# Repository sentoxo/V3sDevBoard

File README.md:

# V3sDevBoard
Educational project of first PCB desgin, SBC with linux built on allwinner V3s SoC.  

## SYSTEM SPECIFICATIONS
=====================

### CORE SYSTEM:
- CPU: Allwinner V3s (ARM Cortex-A7 @ 1.2GHz)
- RAM: 64MB DDR2 @ 400MHz (Integrated SiP)
- STORAGE: SD Interface for OS (SDIO compatible)

### CONNECTIVITY:
- ETHERNET: 100Mbps Interface
- WIRELESS: WiFi & Bluetooth (via ESP32[ESP-Hosted-NG] on SDIO/UART) {PG0-5 -> SDIO, PB0-1 -> UART}
- LONG RANGE: LoRa support (via Ra-02 on SPI) {PB2 -> RESET, PB3 -> INT, PC0-3 -> SPI}
- USB: USB Host support (Simple)
- DEBUG: System UARTs to USB bridge

### DISPLAY & IMAGING:
- CAMERA: MIPI CSI (22-pin connector)
- LCD: RGB-666 Interface with backlight support (40-pin) [ST7280] {PB4 -> LC_LED_PWM, PE0-19,23-24}

### SENSORS & I/O:
- MOTION: MPU6050 Accelerometer & Gyroscope [I2C] {PB6-7}
- ENVIRONMENT: BME280 Sensor (Temp/Press/Hum) [I2C] {PB6-7}
- AUDIO: 3.5mm Audio Jack
- INPUT: Low-resolution ADC for button matrix (6 buttons)
- VISUAL: PCB RGB backlight WS2812B {PB5}

### POWER & SOFTWARE:
- REGULATION: DC-DC converters for 3.3V, 1.8V, 1.2V
- OPERATING SYSTEM: Powered by custom Mainline Linux

=====================
## Errata for revA
- Ther was mistake in SDIO for SDCard. Swaped data lines.
- RTC didn't have power without battery.

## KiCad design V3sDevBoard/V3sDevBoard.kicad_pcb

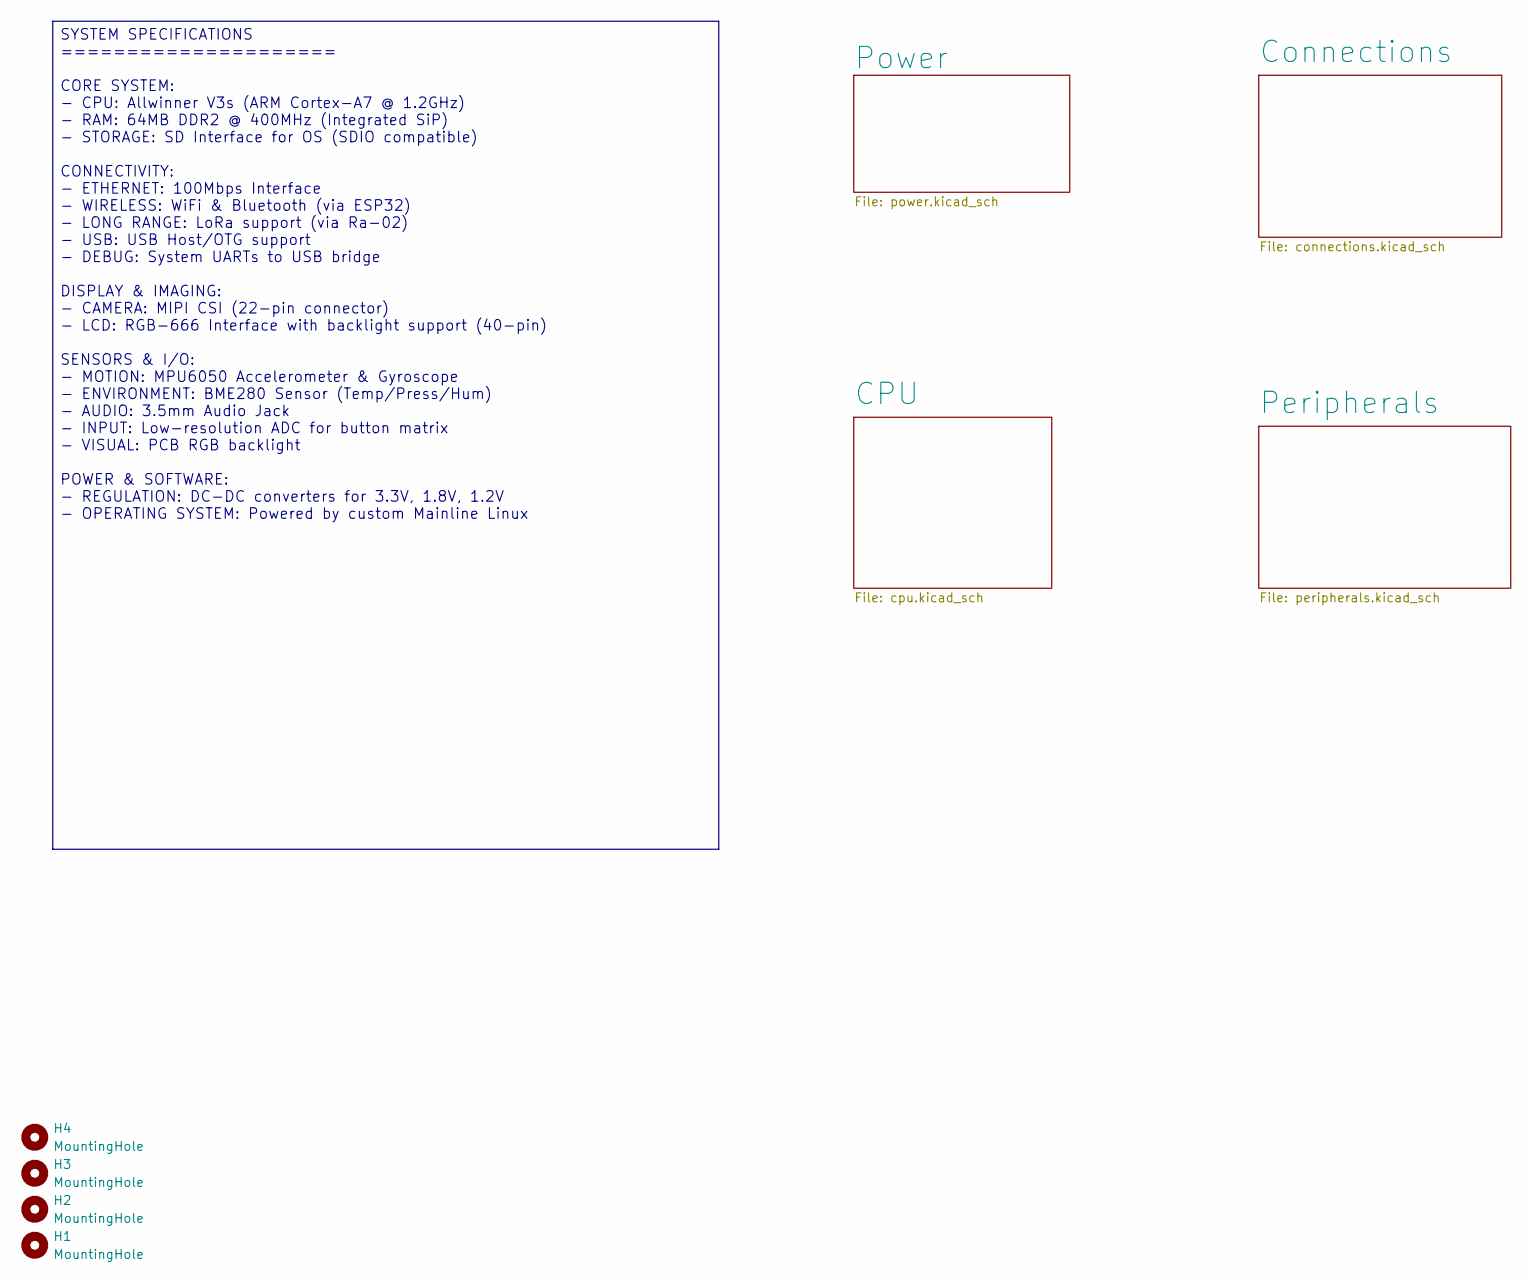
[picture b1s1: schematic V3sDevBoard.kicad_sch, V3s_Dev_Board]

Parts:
H1, H2, H3, H4: MountingHole; MountingHole_3.2mm_M3

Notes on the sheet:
SYSTEM SPECIFICATIONS ===================== CORE SYSTEM: - CPU: Allwinner V3s (ARM Cortex-A7 @ 1.2GHz) - RAM: 64MB DDR2 @ 400MHz (Integrated SiP) - STORAGE: SD Interface for OS (SDIO compatible) CONNECTIVITY: - ETHERNET: 100Mbps Interface - WIRELESS: WiFi & Bluetooth (via ESP32) - LONG RANGE: LoRa 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

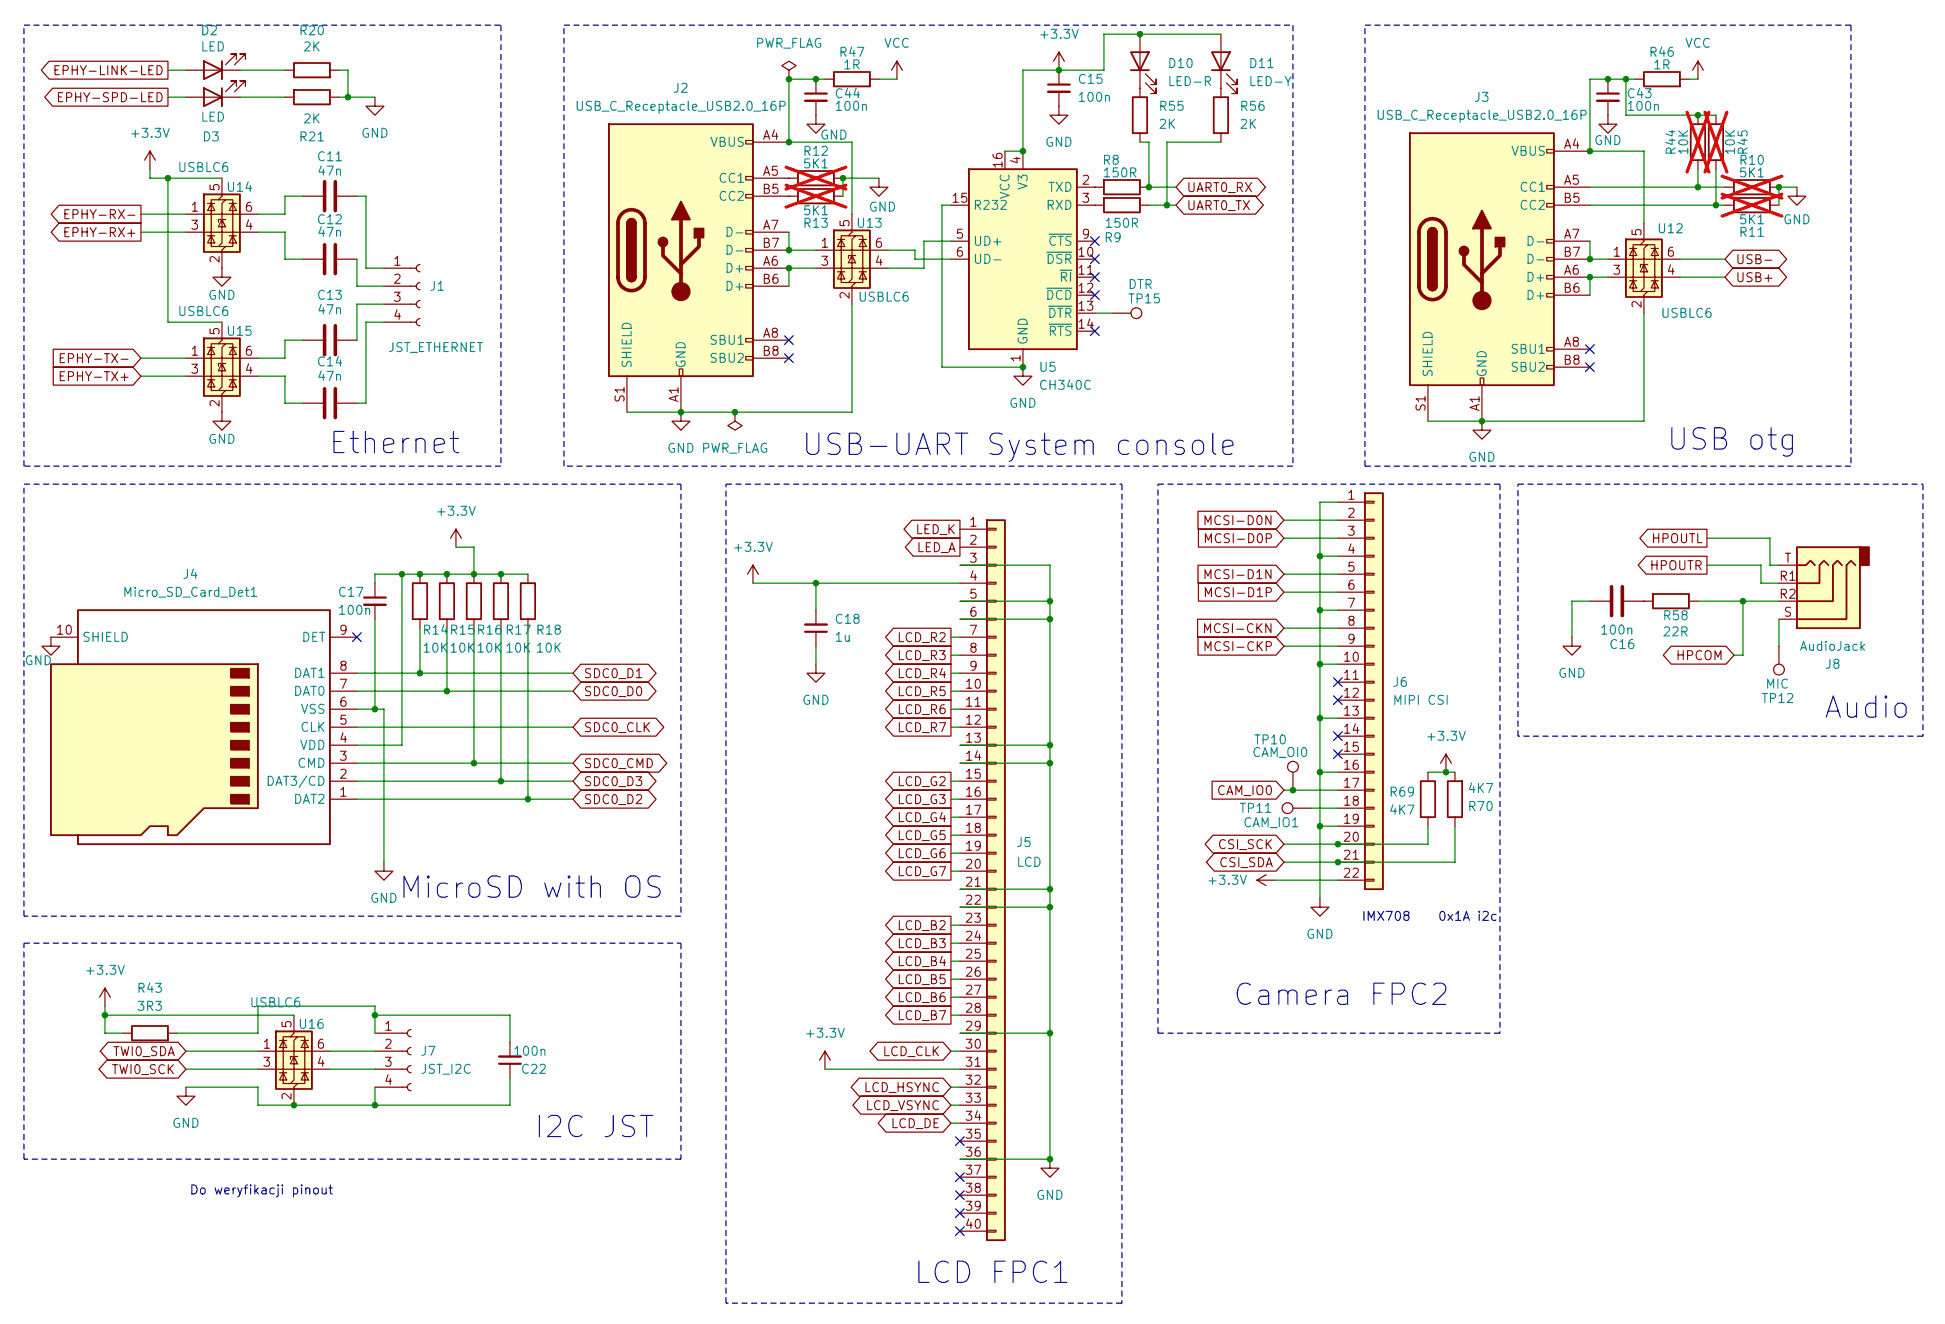
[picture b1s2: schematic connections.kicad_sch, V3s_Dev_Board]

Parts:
C11, C12, C13, C14: 47n; C_0805_2012Metric_Pad1.18x1.45mm_HandSolder
C15, C16, C17, C22: 100n; C_0805_2012Metric_Pad1.18x1.45mm_HandSolder
C18: 1u; C_0805_2012Metric_Pad1.18x1.45mm_HandSolder
C43, C44: 100n; C_0603_1608Metric_Pad1.08x0.95mm_HandSolder
D2, D3: LED; LED_0805_2012Metric_Pad1.15x1.40mm_HandSolder
D10: LED-R; LED_0805_2012Metric_Pad1.15x1.40mm_HandSolder
D11: LED-Y; LED_0805_2012Metric_Pad1.15x1.40mm_HandSolder
J1: JST_ETHERNET; JST_GH_BM04B-GHS-TBT_1x04-1MP_P1.25mm_Vertical
J2, J3: USB_C_Receptacle_USB2.0_16P; USB_C_Receptacle_GCT_USB4105-xx-A_16P_TopMnt_Horizontal
J4: Micro_SD_Card_Det1; microSD
J5: LCD; Amphenol_F32Q-1A7x1-11040_1x40-1MP_P0.5mm_Horizontal
J6: MIPI CSI; FPC_1x22-1MP_P0.5mm_Vertical
J7: JST_I2C; JST_GH_BM04B-GHS-TBT_1x04-1MP_P1.25mm_Vertical
J8: AudioJack; Jack_3.5mm_PJ320D_Horizontal
R8, R9: 150R; R_0603_1608Metric_Pad0.98x0.95mm_HandSolder
R10, R11, R12, R13: 5K1; R_0603_1608Metric_Pad0.98x0.95mm_HandSolder; not fitted
R14, R15, R16, R17, R18: 10K; R_0603_1608Metric_Pad0.98x0.95mm_HandSolder
R20, R21, R55, R56: 2K; R_0603_1608Metric_Pad0.98x0.95mm_HandSolder
R43: 3R3; R_0805_2012Metric_Pad1.20x1.40mm_HandSolder
R44, R45: 10K; R_0603_1608Metric_Pad0.98x0.95mm_HandSolder; not fitted
R46, R47: 1R; R_0805_2012Metric
R58: 22R; R_0603_1608Metric_Pad0.98x0.95mm_HandSolder
R69, R70: 4K7; R_0603_1608Metric_Pad0.98x0.95mm_HandSolder
TP10: CAM_OI0; TestPoint_Pad_D1.0mm
TP11: CAM_IO1; TestPoint_Pad_D1.0mm
TP12: MIC; TestPoint_Pad_D1.0mm
TP15: DTR; TestPoint_Pad_D1.0mm
U5: CH340C; SOIC-16_3.9x9.9mm_P1.27mm
U12, U13, U14, U15, U16: USBLC6; SOT-23-6

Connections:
+3.3V: C15.1, C17.1, C18.2, D10.2 (A), D11.2 (A), J4.4 (VDD), J5.4, J5.31, J6.22, R14.1, R15.1, R16.1, R17.1, R18.1, R43.1, R69.1, R70.2, U5.4 (V3), U5.16 (VCC), U14.5 (VBUS), U15.5 (VBUS), U16.5 (VBUS); also elsewhere on the board
CAM_IO0: J6.17, TP10.1 (1_1); also elsewhere on the board
CSI_SCK: J6.20, R69.2; also elsewhere on the board
CSI_SDA: J6.21, R70.1; also elsewhere on the board
EPHY-LINK-LED: D2.2 (A); also elsewhere on the board
EPHY-RX+: U14.3 (I/O2); also elsewhere on the board
EPHY-RX-: U14.1 (I/O1); also elsewhere on the board
EPHY-SPD-LED: D3.2 (A); also elsewhere on the board
EPHY-TX+: U15.3 (I/O2); also elsewhere on the board
EPHY-TX-: U15.1 (I/O1); also elsewhere on the board
GND: C15.2, C16.2, C17.2, C18.1, C22.1, C43.2, C44.2, J2.A1 (GND), J2.A12 (GND), J2.B1 (GND), J2.B12 (GND), J2.S1 (SHIELD), J3.A1 (GND), J3.A12 (GND), J3.B1 (GND), J3.B12 (GND), J3.S1 (SHIELD), J4.6 (VSS), J4.10 (SHIELD), J5.3, J5.5, J5.6, J5.13, J5.14, J5.21, J5.22, J5.29, J5.36, J6.1, J6.4, J6.7, J6.10, J6.13, J6.16, J6.19, J7.4, R10.2, R11.1, R12.2, R13.1, R20.2, R21.1, U5.1 (GND), U5.15 (R232), U12.2 (GND), U13.2 (GND), U14.2 (GND), U15.2 (GND), U16.2 (GND); also elsewhere on the board
HPCOM: J8.R2, R58.1; also elsewhere on the board
HPOUTL: J8.T; also elsewhere on the board
HPOUTR: J8.R1; also elsewhere on the board
LCD_B2: J5.23; also elsewhere on the board
LCD_B3: J5.24; also elsewhere on the board
LCD_B4: J5.25; also elsewhere on the board
LCD_B5: J5.26; also elsewhere on the board
LCD_B6: J5.27; also elsewhere on the board
LCD_B7: J5.28; also elsewhere on the board
LCD_CLK: J5.30; also elsewhere on the board
LCD_DE: J5.34; also elsewhere on the board
LCD_G2: J5.15; also elsewhere on the board
LCD_G3: J5.16; also elsewhere on the board
LCD_G4: J5.17; also elsewhere on the board
LCD_G5: J5.18; also elsewhere on the board
LCD_G6: J5.19; also elsewhere on the board
LCD_G7: J5.20; also elsewhere on the board
LCD_HSYNC: J5.32; also elsewhere on the board
LCD_R2: J5.7; also elsewhere on the board
LCD_R3: J5.8; also elsewhere on the board
LCD_R4: J5.9; also elsewhere on the board
LCD_R5: J5.10; also elsewhere on the board
LCD_R6: J5.11; also elsewhere on the board
LCD_R7: J5.12; also elsewhere on the board
LCD_VSYNC: J5.33; also elsewhere on the board
LED_A: J5.2; also elsewhere on the board
LED_K: J5.1; also elsewhere on the board
MCSI-CKN: J6.8; also elsewhere on the board
MCSI-CKP: J6.9; also elsewhere on the board
MCSI-D0N: J6.2; also elsewhere on the board
MCSI-D0P: J6.3; also elsewhere on the board
MCSI-D1N: J6.5; also elsewhere on the board
MCSI-D1P: J6.6; also elsewhere on the board
unnamed: C11.1, U14.6 (I/O1)
unnamed: C12.1, U14.4 (I/O2)
unnamed: C13.1, U15.6 (I/O1)
unnamed: C14.1, U15.4 (I/O2)
unnamed: C16.1, R58.2
unnamed: D2.1 (K), R20.1
unnamed: D3.1 (K), R21.2
unnamed: D10.1 (K), R55.1
unnamed: D11.1 (K), R56.1
unnamed: C11.2, J1.1
unnamed: C12.2, J1.2
unnamed: C13.2, J1.3
unnamed: C14.2, J1.4
unnamed: J2.A5 (CC1), R12.1
unnamed: J2.B5 (CC2), R13.2
unnamed: J2.A6 (D+), J2.B6 (D+), U13.3 (I/O2)
unnamed: J2.A7 (D-), J2.B7 (D-), U13.1 (I/O1)
unnamed: J3.A5 (CC1), R10.1, R44.1
unnamed: J3.B5 (CC2), R11.2, R45.2
unnamed: J3.A6 (D+), J3.B6 (D+), U12.3 (I/O2)
unnamed: J3.A7 (D-), J3.B7 (D-), U12.1 (I/O1)
unnamed: J6.18, TP11.1 (1_1)
unnamed: C22.2, J7.1, R43.2
unnamed: J7.2, U16.6 (I/O1)
unnamed: J7.3, U16.4 (I/O2)
unnamed: J8.S, TP12.1 (1_1)
unnamed: R9.2, U5.3 (RXD)
unnamed: R8.2, U5.2 (TXD)
unnamed: U5.5 (UD+), U13.4 (I/O2)
unnamed: U5.6 (UD-), U13.6 (I/O1)
unnamed: TP15.1 (1_1), U5.13 (~DTR)
unnamed: C43.1, J3.A4 (VBUS), J3.A9 (VBUS), J3.B4 (VBUS), J3.B9 (VBUS), R44.2, R45.1, R46.1, U12.5 (VBUS)
unnamed: C44.1, J2.A4 (VBUS), J2.A9 (VBUS), J2.B4 (VBUS), J2.B9 (VBUS), R47.1, U13.5 (VBUS)
SDC0_CLK: J4.5 (CLK); also elsewhere on the board
SDC0_CMD: J4.3 (CMD), R16.2; also elsewhere on the board
SDC0_D0: J4.7 (DAT0), R15.2; also elsewhere on the board
SDC0_D1: J4.8 (DAT1), R14.2; also elsewhere on the board
SDC0_D2: J4.1 (DAT2), R18.2; also elsewhere on the board
SDC0_D3: J4.2 (DAT3/CD), R17.2; also elsewhere on the board
TWI0_SCK: U16.3 (I/O2); also elsewhere on the board
TWI0_SDA: U16.1 (I/O1); also elsewhere on the board
UART0_RX: R8.1, R55.2; also elsewhere on the board
UART0_TX: R9.1, R56.2; also elsewhere on the board
USB+: U12.4 (I/O2); also elsewhere on the board
USB-: U12.6 (I/O1); also elsewhere on the board
VCC: R46.2, R47.2; also elsewhere on the board

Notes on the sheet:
MicroSD with OS
LCD FPC1
Ethernet
Camera FPC2
USB otg
Audio
IMX708 0x1A i2c
USB-UART System console
Do weryfikacji pinout
I2C JST

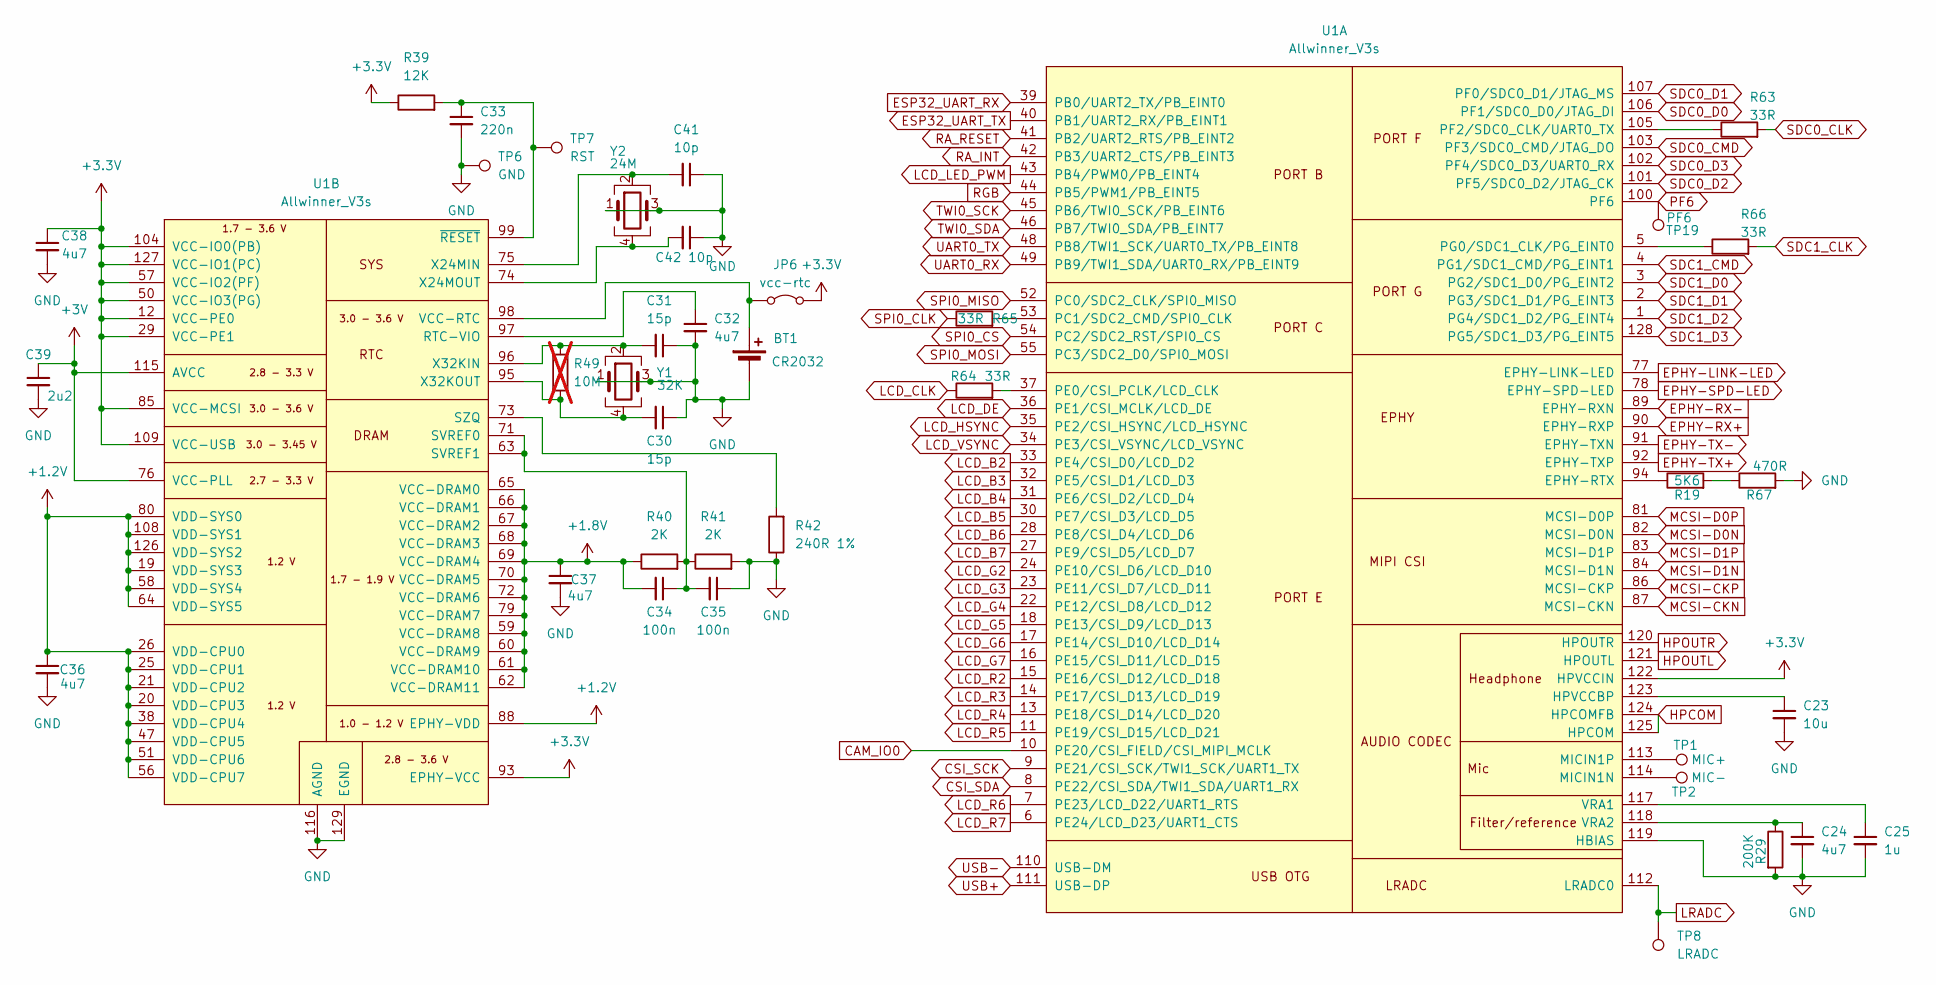
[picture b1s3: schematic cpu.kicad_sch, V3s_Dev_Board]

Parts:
BT1: CR2032; PinHeader_1x02_P1.00mm_Vertical_SMD_Pin1Right
C23: 10u; C_0805_2012Metric_Pad1.18x1.45mm_HandSolder
C24, C32, C36, C37, C38: 4u7; C_0805_2012Metric_Pad1.18x1.45mm_HandSolder
C25: 1u; C_0805_2012Metric_Pad1.18x1.45mm_HandSolder
C30, C31: 15p; C_0603_1608Metric_Pad1.08x0.95mm_HandSolder
C33: 220n; C_0603_1608Metric_Pad1.08x0.95mm_HandSolder
C34, C35: 100n; C_0603_1608Metric_Pad1.08x0.95mm_HandSolder
C39: 2u2; C_0805_2012Metric_Pad1.18x1.45mm_HandSolder
C41, C42: 10p; C_0603_1608Metric_Pad1.08x0.95mm_HandSolder
JP6: vcc-rtc; SolderJumper-2_P1.3mm_Bridged_RoundedPad1.0x1.5mm
R19: 5K6; R_0603_1608Metric_Pad0.98x0.95mm_HandSolder
R29: 200K; R_0603_1608Metric_Pad0.98x0.95mm_HandSolder
R39: 12K; R_0603_1608Metric_Pad0.98x0.95mm_HandSolder
R40, R41: 2K; R_0603_1608Metric_Pad0.98x0.95mm_HandSolder
R42: 240R 1%; R_0603_1608Metric_Pad0.98x0.95mm_HandSolder
R49: 10M; R_0603_1608Metric_Pad0.98x0.95mm_HandSolder; not fitted
R63, R64, R65, R66: 33R; R_0603_1608Metric_Pad0.98x0.95mm_HandSolder
R67: 470R; R_0603_1608Metric_Pad0.98x0.95mm_HandSolder
TP1: MIC+; TestPoint_Pad_1.0x1.0mm
TP2: MIC-; TestPoint_Pad_1.0x1.0mm
TP6: GND; TestPoint_Pad_D1.5mm
TP7: RST; TestPoint_Pad_D1.5mm
TP8: LRADC; TestPoint_Pad_D1.0mm
TP19: PF6; TestPoint_Pad_D1.0mm
U1: Allwinner_V3s; eLQFP-128_14x14_Pitch0.4mm_EPAD_6.60mm
Y1: 32K; Crystal_SMD_3225-4Pin_3.2x2.5mm_HandSoldering
Y2: 24M; Crystal_SMD_3225-4Pin_3.2x2.5mm_HandSoldering

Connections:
+1.2V: C36.1, U1.19 (VDD-SYS3), U1.20 (VDD-CPU3), U1.21 (VDD-CPU2), U1.25 (VDD-CPU1), U1.26 (VDD-CPU0), U1.38 (VDD-CPU4), U1.47 (VDD-CPU5), U1.51 (VDD-CPU6), U1.56 (VDD-CPU7), U1.58 (VDD-SYS4), U1.64 (VDD-SYS5), U1.80 (VDD-SYS0), U1.88 (EPHY-VDD), U1.108 (VDD-SYS1), U1.126 (VDD-SYS2); also elsewhere on the board
+1.8V: C34.2, C37.1, R40.1, U1.59 (VCC-DRAM8), U1.60 (VCC-DRAM9), U1.61 (VCC-DRAM10), U1.62 (VCC-DRAM11), U1.65 (VCC-DRAM0), U1.66 (VCC-DRAM1), U1.67 (VCC-DRAM2), U1.68 (VCC-DRAM3), U1.69 (VCC-DRAM4), U1.70 (VCC-DRAM5), U1.72 (VCC-DRAM6), U1.79 (VCC-DRAM7); also elsewhere on the board
+3.3V: C38.1, JP6.2 (B), R39.1, U1.12 (VCC-PE0), U1.29 (VCC-PE1), U1.50 (VCC-IO3(PG)), U1.57 (VCC-IO2(PF)), U1.85 (VCC-MCSI), U1.93 (EPHY-VCC), U1.104 (VCC-IO0(PB)), U1.109 (VCC-USB), U1.122 (HPVCCIN), U1.127 (VCC-IO1(PC)); also elsewhere on the board
+3V: C39.1, U1.76 (VCC-PLL), U1.115 (AVCC); also elsewhere on the board
CAM_IO0: U1.10 (PE20/CSI_FIELD/CSI_MIPI_MCLK); also elsewhere on the board
CSI_SCK: U1.9 (PE21/CSI_SCK/TWI1_SCK/UART1_TX); also elsewhere on the board
CSI_SDA: U1.8 (PE22/CSI_SDA/TWI1_SDA/UART1_RX); also elsewhere on the board
EPHY-LINK-LED: U1.77 (EPHY-LINK-LED); also elsewhere on the board
EPHY-RX+: U1.90 (EPHY-RXP); also elsewhere on the board
EPHY-RX-: U1.89 (EPHY-RXN); also elsewhere on the board
EPHY-SPD-LED: U1.78 (EPHY-SPD-LED); also elsewhere on the board
EPHY-TX+: U1.92 (EPHY-TXP); also elsewhere on the board
EPHY-TX-: U1.91 (EPHY-TXN); also elsewhere on the board
ESP32_UART_RX: U1.39 (PB0/UART2_TX/PB_EINT0); also elsewhere on the board
ESP32_UART_TX: U1.40 (PB1/UART2_RX/PB_EINT1); also elsewhere on the board
GND: BT1.2 (-), C23.2, C24.2, C25.2, C30.1, C31.1, C32.2, C33.2, C35.1, C36.2, C37.2, C38.2, C39.2, C41.1, C42.1, R29.2, R41.2, R42.1, R67.2, TP6.1 (1_1), U1.116 (AGND), U1.119 (HBIAS), U1.129 (EGND), Y1.1, Y1.3, Y2.1, Y2.3; also elsewhere on the board
HPCOM: U1.124 (HPCOMFB), U1.125 (HPCOM); also elsewhere on the board
HPOUTL: U1.121 (HPOUTL); also elsewhere on the board
HPOUTR: U1.120 (HPOUTR); also elsewhere on the board
LCD_B2: U1.33 (PE4/CSI_D0/LCD_D2); also elsewhere on the board
LCD_B3: U1.32 (PE5/CSI_D1/LCD_D3); also elsewhere on the board
LCD_B4: U1.31 (PE6/CSI_D2/LCD_D4); also elsewhere on the board
LCD_B5: U1.30 (PE7/CSI_D3/LCD_D5); also elsewhere on the board
LCD_B6: U1.28 (PE8/CSI_D4/LCD_D6); also elsewhere on the board
LCD_B7: U1.27 (PE9/CSI_D5/LCD_D7); also elsewhere on the board
LCD_CLK: R64.1; also elsewhere on the board
LCD_DE: U1.36 (PE1/CSI_MCLK/LCD_DE); also elsewhere on the board
LCD_G2: U1.24 (PE10/CSI_D6/LCD_D10); also elsewhere on the board
LCD_G3: U1.23 (PE11/CSI_D7/LCD_D11); also elsewhere on the board
LCD_G4: U1.22 (PE12/CSI_D8/LCD_D12); also elsewhere on the board
LCD_G5: U1.18 (PE13/CSI_D9/LCD_D13); also elsewhere on the board
LCD_G6: U1.17 (PE14/CSI_D10/LCD_D14); also elsewhere on the board
LCD_G7: U1.16 (PE15/CSI_D11/LCD_D15); also elsewhere on the board
LCD_HSYNC: U1.35 (PE2/CSI_HSYNC/LCD_HSYNC); also elsewhere on the board
LCD_LED_PWM: U1.43 (PB4/PWM0/PB_EINT4); also elsewhere on the board
LCD_R2: U1.15 (PE16/CSI_D12/LCD_D18); also elsewhere on the board
LCD_R3: U1.14 (PE17/CSI_D13/LCD_D19); also elsewhere on the board
LCD_R4: U1.13 (PE18/CSI_D14/LCD_D20); also elsewhere on the board
LCD_R5: U1.11 (PE19/CSI_D15/LCD_D21); also elsewhere on the board
LCD_R6: U1.7 (PE23/LCD_D22/UART1_RTS); also elsewhere on the board
LCD_R7: U1.6 (PE24/LCD_D23/UART1_CTS); also elsewhere on the board
LCD_VSYNC: U1.34 (PE3/CSI_VSYNC/LCD_VSYNC); also elsewhere on the board
LRADC: TP8.1 (1_1), U1.112 (LRADC0); also elsewhere on the board
MCSI-CKN: U1.87 (MCSI-CKN); also elsewhere on the board
MCSI-CKP: U1.86 (MCSI-CKP); also elsewhere on the board
MCSI-D0N: U1.82 (MCSI-D0N); also elsewhere on the board
MCSI-D0P: U1.81 (MCSI-D0P); also elsewhere on the board
MCSI-D1N: U1.84 (MCSI-D1N); also elsewhere on the board
MCSI-D1P: U1.83 (MCSI-D1P); also elsewhere on the board
unnamed: BT1.1 (+), JP6.1 (A), U1.98 (VCC-RTC)
unnamed: R19.2, R67.1
unnamed: R19.1, U1.94 (EPHY-RTX)
unnamed: C23.1, U1.123 (HPVCCBP)
unnamed: TP2.1 (1_1), U1.114 (MICIN1N)
unnamed: TP1.1 (1_1), U1.113 (MICIN1P)
unnamed: R65.2, U1.53 (PC1/SDC2_CMD/SPI0_CLK)
unnamed: R64.2, U1.37 (PE0/CSI_PCLK/LCD_CLK)
unnamed: R63.1, U1.105 (PF2/SDC0_CLK/UART0_TX)
unnamed: R66.1, U1.5 (PG0/SDC1_CLK/PG_EINT0)
unnamed: C25.1, U1.117 (VRA1)
unnamed: C24.1, R29.1, U1.118 (VRA2)
unnamed: C32.1, U1.97 (RTC-VIO)
unnamed: C34.1, C35.2, R40.2, R41.1, U1.63 (SVREF1), U1.71 (SVREF0)
unnamed: R42.2, U1.73 (SZQ)
unnamed: C41.2, U1.75 (X24MIN), Y2.2
unnamed: C42.2, U1.74 (X24MOUT), Y2.4
unnamed: C31.2, R49.2, U1.96 (X32KIN), Y1.2
unnamed: C30.2, R49.1, U1.95 (X32KOUT), Y1.4
unnamed: C33.1, R39.2, TP7.1 (1_1), U1.99 (~RESET)
PF6: TP19.1 (1_1), U1.100 (PF6); also elsewhere on the board
RA_INT: U1.42 (PB3/UART2_CTS/PB_EINT3); also elsewhere on the board
RA_RESET: U1.41 (PB2/UART2_RTS/PB_EINT2); also elsewhere on the board
RGB: U1.44 (PB5/PWM1/PB_EINT5); also elsewhere on the board
SDC0_CLK: R63.2; also elsewhere on the board
SDC0_CMD: U1.103 (PF3/SDC0_CMD/JTAG_DO); also elsewhere on the board
SDC0_D0: U1.106 (PF1/SDC0_D0/JTAG_DI); also elsewhere on the board
SDC0_D1: U1.107 (PF0/SDC0_D1/JTAG_MS); also elsewhere on the board
SDC0_D2: U1.101 (PF5/SDC0_D2/JTAG_CK); also elsewhere on the board
SDC0_D3: U1.102 (PF4/SDC0_D3/UART0_RX); also elsewhere on the board
SDC1_CLK: R66.2; also elsewhere on the board
SDC1_CMD: U1.4 (PG1/SDC1_CMD/PG_EINT1); also elsewhere on the board
SDC1_D0: U1.3 (PG2/SDC1_D0/PG_EINT2); also elsewhere on the board
SDC1_D1: U1.2 (PG3/SDC1_D1/PG_EINT3); also elsewhere on the board
SDC1_D2: U1.1 (PG4/SDC1_D2/PG_EINT4); also elsewhere on the board
SDC1_D3: U1.128 (PG5/SDC1_D3/PG_EINT5); also elsewhere on the board
SPI0_CLK: R65.1; also elsewhere on the board
SPI0_CS: U1.54 (PC2/SDC2_RST/SPI0_CS); also elsewhere on the board
SPI0_MISO: U1.52 (PC0/SDC2_CLK/SPI0_MISO); also elsewhere on the board
SPI0_MOSI: U1.55 (PC3/SDC2_D0/SPI0_MOSI); also elsewhere on the board
TWI0_SCK: U1.45 (PB6/TWI0_SCK/PB_EINT6); also elsewhere on the board
TWI0_SDA: U1.46 (PB7/TWI0_SDA/PB_EINT7); also elsewhere on the board
UART0_RX: U1.49 (PB9/TWI1_SDA/UART0_RX/PB_EINT9); also elsewhere on the board
UART0_TX: U1.48 (PB8/TWI1_SCK/UART0_TX/PB_EINT8); also elsewhere on the board
USB+: U1.111 (USB-DP); also elsewhere on the board
USB-: U1.110 (USB-DM); also elsewhere on the board

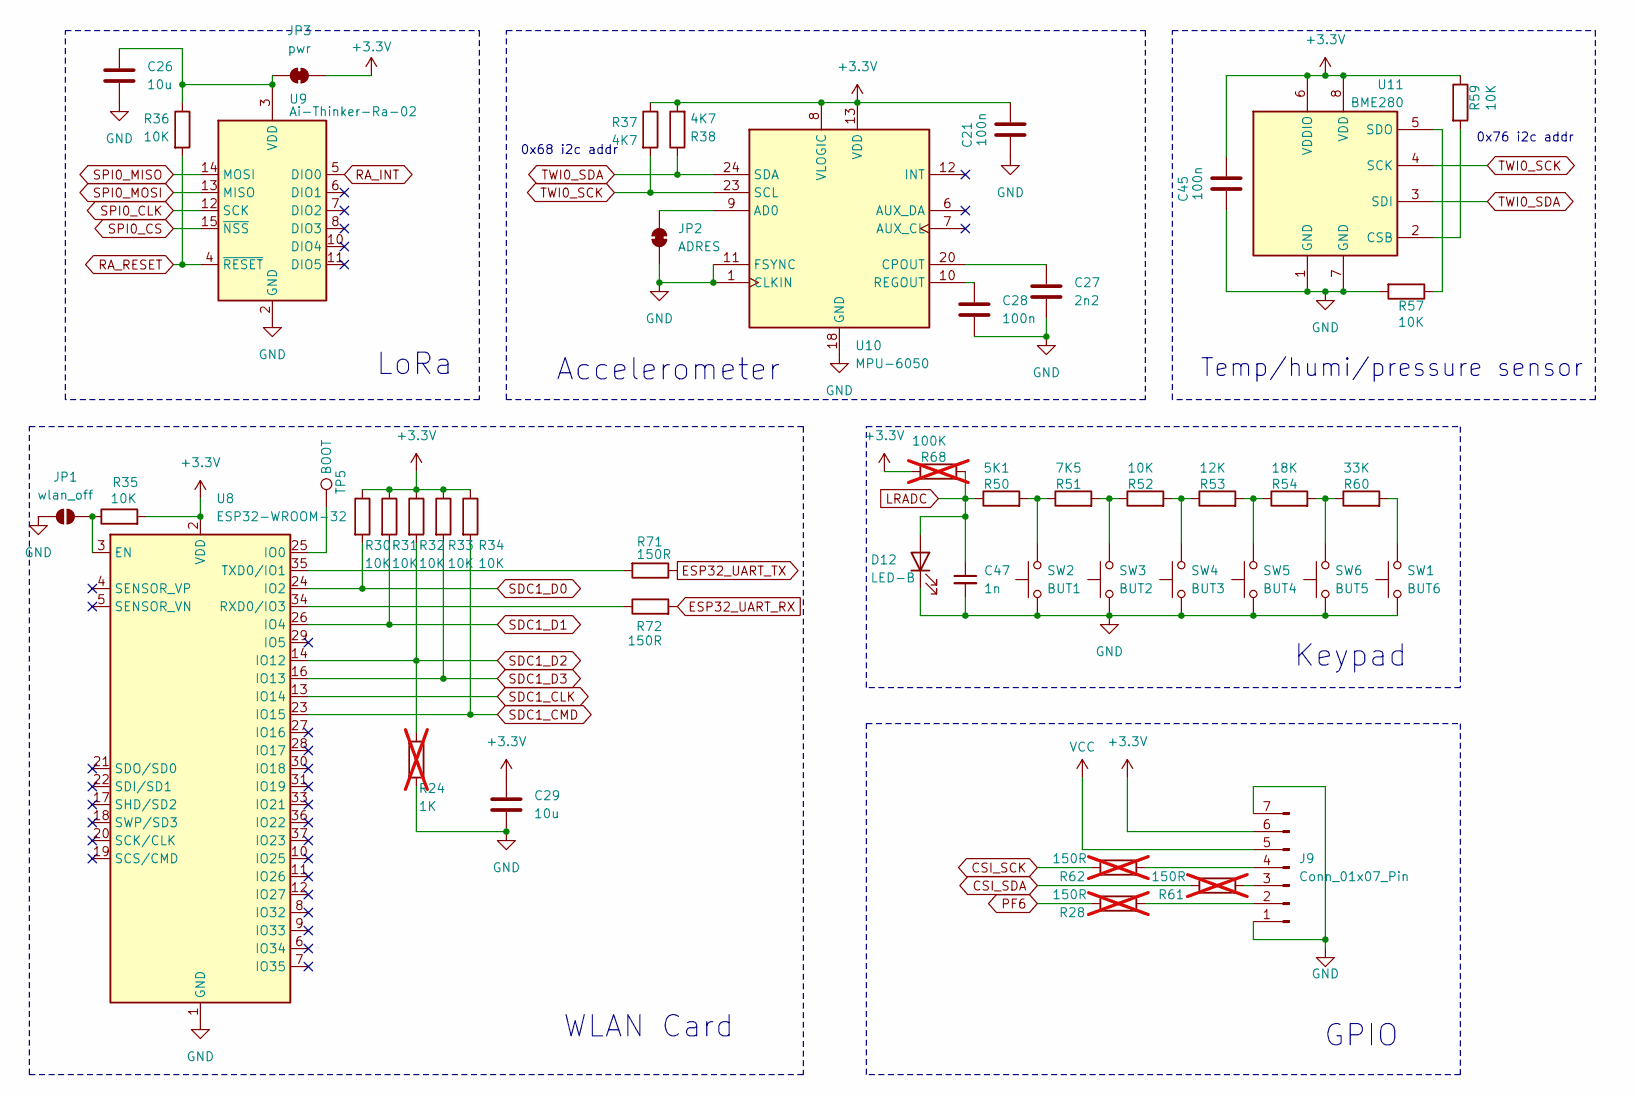
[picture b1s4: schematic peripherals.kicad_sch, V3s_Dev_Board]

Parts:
C21, C45: 100n; C_0805_2012Metric_Pad1.18x1.45mm_HandSolder
C26, C29: 10u; C_1206_3216Metric
C27: 2n2; C_0603_1608Metric_Pad1.08x0.95mm_HandSolder
C28: 100n; C_0603_1608Metric_Pad1.08x0.95mm_HandSolder
C47: 1n; C_0805_2012Metric_Pad1.18x1.45mm_HandSolder
D12: LED-B; LED_0805_2012Metric_Pad1.15x1.40mm_HandSolder
J9: Conn_01x07_Pin; PinHeader_1x07_P2.54mm_Vertical
JP1: wlan_off; SolderJumper-2_P1.3mm_Open_RoundedPad1.0x1.5mm
JP2: ADRES; SolderJumper-2_P1.3mm_Bridged_RoundedPad1.0x1.5mm
JP3: pwr; SolderJumper-2_P1.3mm_Bridged_RoundedPad1.0x1.5mm
R24: 1K; R_0603_1608Metric_Pad0.98x0.95mm_HandSolder; not fitted
R28, R61, R62: 150R; R_0603_1608Metric_Pad0.98x0.95mm_HandSolder; not fitted
R30, R31, R32, R33, R34, R35, R36, R52, R57, R59: 10K; R_0603_1608Metric_Pad0.98x0.95mm_HandSolder
R37, R38: 4K7; R_0603_1608Metric_Pad0.98x0.95mm_HandSolder
R50: 5K1; R_0603_1608Metric_Pad0.98x0.95mm_HandSolder
R51: 7K5; R_0603_1608Metric_Pad0.98x0.95mm_HandSolder
R53: 12K; R_0603_1608Metric_Pad0.98x0.95mm_HandSolder
R54: 18K; R_0603_1608Metric_Pad0.98x0.95mm_HandSolder
R60: 33K; R_0603_1608Metric_Pad0.98x0.95mm_HandSolder
R68: 100K; R_0603_1608Metric_Pad0.98x0.95mm_HandSolder; not fitted
R71, R72: 150R; R_0603_1608Metric_Pad0.98x0.95mm_HandSolder
SW1: BUT6; Button_6x3mm
SW2: BUT1; Button_6x3mm
SW3: BUT2; Button_6x3mm
SW4: BUT3; Button_6x3mm
SW5: BUT4; Button_6x3mm
SW6: BUT5; Button_6x3mm
TP5: BOOT; TestPoint_Pad_D1.0mm
U8: ESP32-WROOM-32
U9: Ai-Thinker-Ra-02; Ai-Thinker-Ra-01-LoRa
U10: MPU-6050; InvenSense_QFN-24_4x4mm_P0.5mm
U11: BME280; Bosch_LGA-8_2.5x2.5mm_P0.65mm_ClockwisePinNumbering

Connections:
+3.3V: C21.2, C29.1, C45.2, J9.6, JP3.1 (A), R30.1, R31.1, R32.1, R33.1, R34.1, R35.2, R37.1, R38.2, R59.1, R68.1, U8.2 (VDD), U10.8 (VLOGIC), U10.13 (VDD), U11.6 (VDDIO), U11.8 (VDD); also elsewhere on the board
CSI_SCK: R62.1; also elsewhere on the board
CSI_SDA: R61.1; also elsewhere on the board
ESP32_UART_RX: R72.2; also elsewhere on the board
ESP32_UART_TX: R71.1; also elsewhere on the board
GND: C21.1, C26.2, C27.2, C28.2, C29.2, C45.1, C47.2, D12.1 (K), J9.1, J9.7, JP1.1 (A), JP2.2 (B), R24.2, R57.2, SW1.1, SW2.1, SW3.1, SW4.1, SW5.1, SW6.1, U8.1 (GND), U8.15 (GND), U8.38 (GND), U8.39 (GND), U9.1 (GND), U9.2 (GND), U9.9 (GND), U9.16 (GND), U10.1 (CLKIN), U10.11 (FSYNC), U10.18 (GND), U11.1 (GND), U11.7 (GND); also elsewhere on the board
LRADC: C47.1, D12.2 (A), R50.1, R68.2; also elsewhere on the board
unnamed: J9.2, R28.2
unnamed: J9.3, R61.2
unnamed: J9.4, R62.2
unnamed: JP1.2 (B), R35.1, U8.3 (EN)
unnamed: JP2.1 (A), U10.9 (AD0)
unnamed: C26.1, JP3.2 (B), R36.1, U9.3 (VDD)
unnamed: R50.2, R51.1, SW2.2
unnamed: R51.2, R52.1, SW3.2
unnamed: R52.2, R53.1, SW4.2
unnamed: R53.2, R54.1, SW5.2
unnamed: R54.2, R60.1, SW6.2
unnamed: R60.2, SW1.2
unnamed: TP5.1 (1_1), U8.25 (IO0)
unnamed: R72.1, U8.34 (RXD0/IO3)
unnamed: R71.2, U8.35 (TXD0/IO1)
unnamed: C27.1, U10.20 (CPOUT)
unnamed: C28.1, U10.10 (REGOUT)
unnamed: R59.2, U11.2 (CSB)
unnamed: R57.1, U11.5 (SDO)
PF6: R28.1; also elsewhere on the board
RA_INT: U9.5 (DIO0); also elsewhere on the board
RA_RESET: R36.2, U9.4 (~RESET); also elsewhere on the board
SDC1_CLK: U8.13 (IO14); also elsewhere on the board
SDC1_CMD: R34.2, U8.23 (IO15); also elsewhere on the board
SDC1_D0: R30.2, U8.24 (IO2); also elsewhere on the board
SDC1_D1: R31.2, U8.26 (IO4); also elsewhere on the board
SDC1_D2: R24.1, R32.2, U8.14 (IO12); also elsewhere on the board
SDC1_D3: R33.2, U8.16 (IO13); also elsewhere on the board
SPI0_CLK: U9.12 (SCK); also elsewhere on the board
SPI0_CS: U9.15 (~NSS); also elsewhere on the board
SPI0_MISO: U9.14 (MOSI); also elsewhere on the board
SPI0_MOSI: U9.13 (MISO); also elsewhere on the board
TWI0_SCK: R37.2, U10.23 (SCL), U11.4 (SCK); also elsewhere on the board
TWI0_SDA: R38.1, U10.24 (SDA), U11.3 (SDI); also elsewhere on the board
VCC: J9.5; also elsewhere on the board

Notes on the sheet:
0x68 i2c addr
Keypad
LoRa
Temp/humi/pressure sensor
0x76 i2c addr
WLAN Card
Accelerometer
GPIO
